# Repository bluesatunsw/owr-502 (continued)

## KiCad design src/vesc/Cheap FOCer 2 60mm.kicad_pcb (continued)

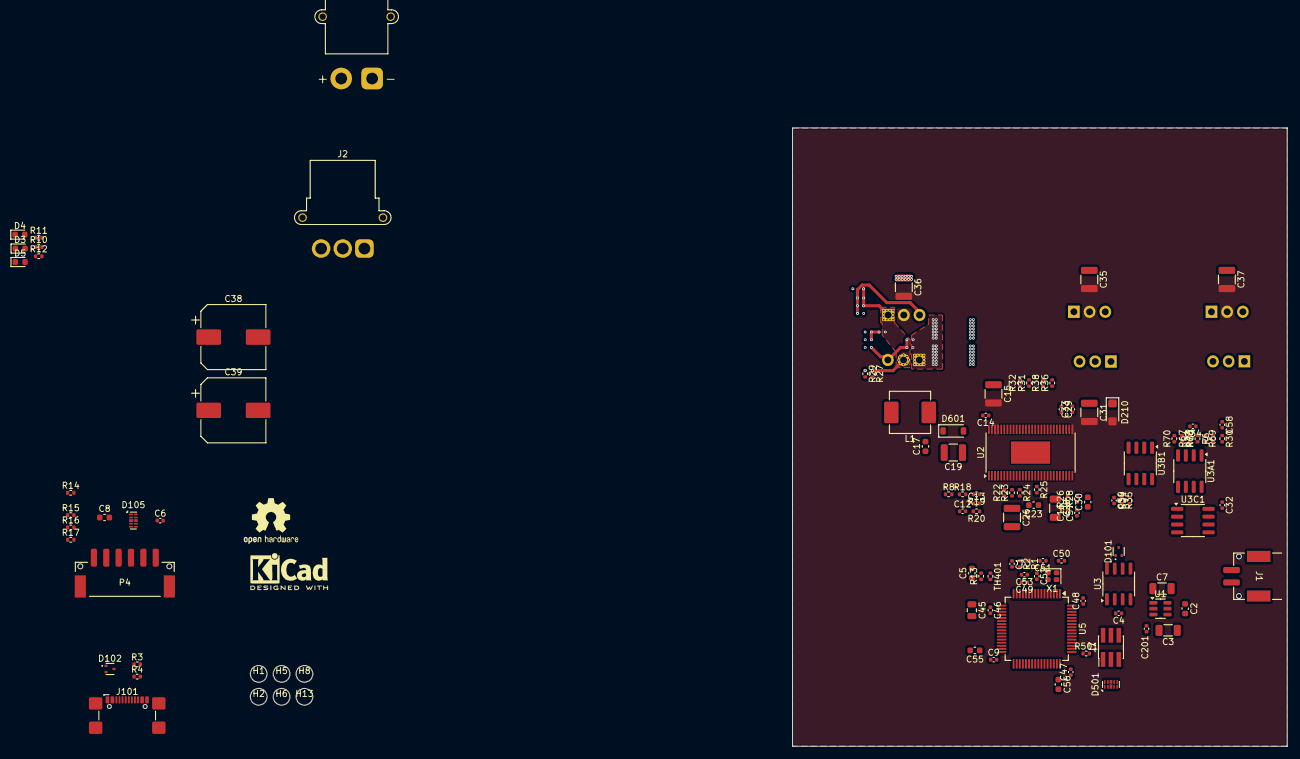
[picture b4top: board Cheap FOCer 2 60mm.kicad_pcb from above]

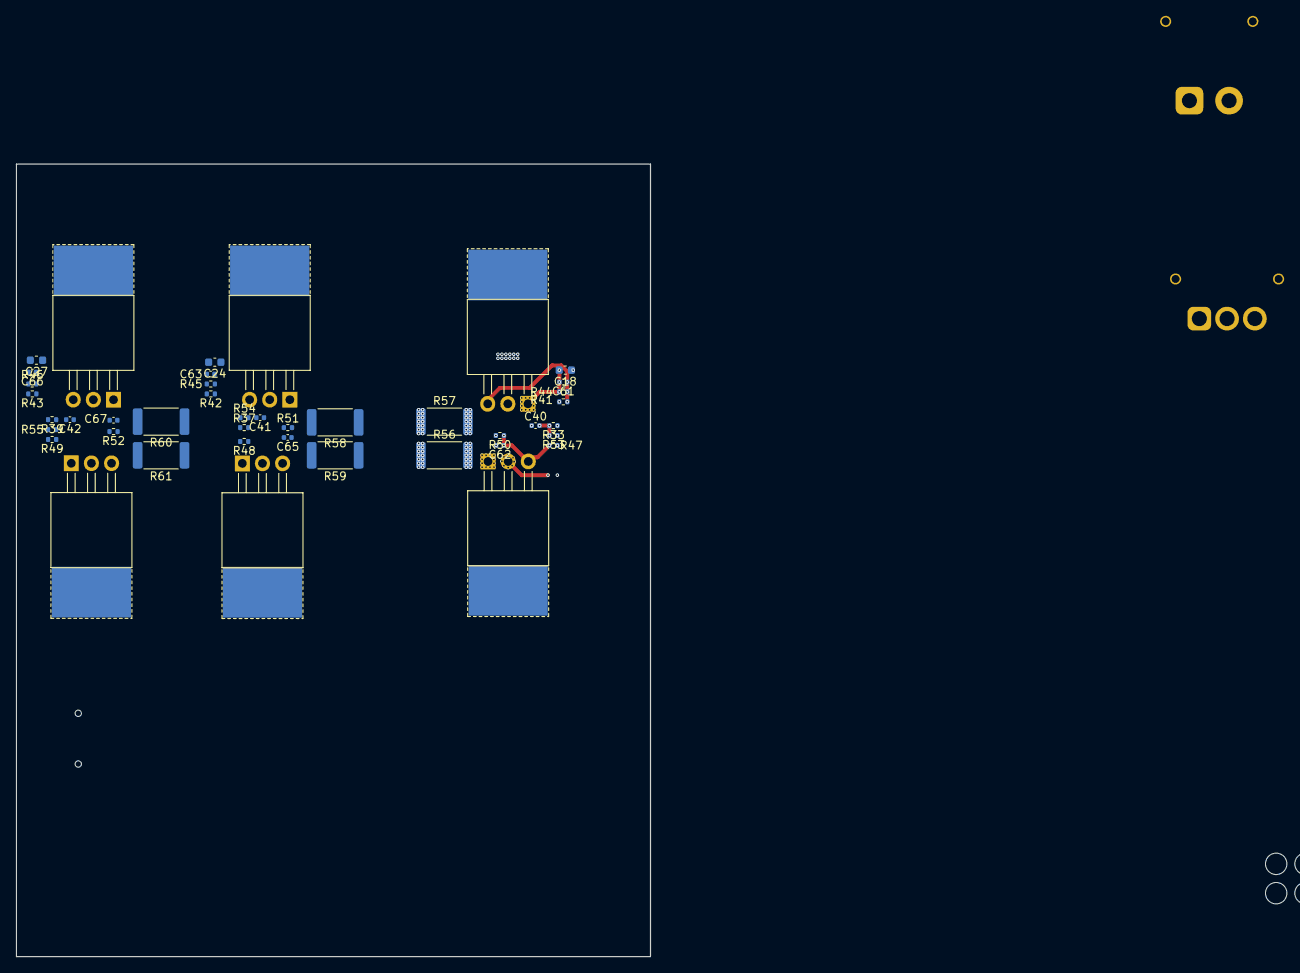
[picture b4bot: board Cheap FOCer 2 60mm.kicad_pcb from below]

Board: 6 copper layers, 80.0 x 100.0 mm, 158 parts (42 on the bottom side), 99 nets.

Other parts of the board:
C2, C8: 2u2; C_0603_1608Metric
C3, C7: 10u; C_1206_3216Metric
C9, C201: 220n; C_0402_1005Metric
D101, D102: 5V; SOT-523
D105: 3V3; Diodes_UDFN-10_1.0x2.5mm_P0.5mm
J2: Conn_01x03; AMASS_MR30PW-FB_1x03_P3.50mm_Horizontal
J101: USB_C_Receptacle_USB2.0_16P; USB_C_Receptacle_GCT_USB4110
U1: HX4002; SOT-23-6

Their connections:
/CAN bus transceiver/CANH: D101.1; also elsewhere on the board
/CAN bus transceiver/CANL: D101.2; also elsewhere on the board
/Filters/HALL1_IN: D105.4, D105.7; also elsewhere on the board
/Filters/HALL2_IN: D105.2, D105.9; also elsewhere on the board
/Filters/TEMP_IN: D105.5, D105.6; also elsewhere on the board
/HALL3: D105.1, D105.10; also elsewhere on the board
/Mosfet driver/H1_VS: J2.1; also elsewhere on the board
/Mosfet driver/H2_VS: J2.2; also elsewhere on the board
/Mosfet driver/H3_VS: J2.3; also elsewhere on the board
GND: C3.2, C7.2, C8.2, C9.1, C201.2, D101.3, D102.3, D105.3, D105.8, J101.A1 (GND), J101.A12 (GND), J101.B1 (GND), J101.B12 (GND), J101.S1 (SHIELD), U1.2 (GND); also elsewhere on the board
unnamed 56: D102.1, J101.A7 (D-), J101.B7 (D-); also elsewhere on the board
unnamed 57: D102.2, J101.A6 (D+), J101.B6 (D+); also elsewhere on the board
unnamed: C2.1, U1.6 (CP+)
unnamed: C2.2, U1.4 (CP-)
unnamed 71: C7.1, U1.1 (VOUT); also elsewhere on the board
VCC: C3.1, C8.1, C9.2, C201.1, U1.3 (~SHDN), U1.5 (VIN); also elsewhere on the board
